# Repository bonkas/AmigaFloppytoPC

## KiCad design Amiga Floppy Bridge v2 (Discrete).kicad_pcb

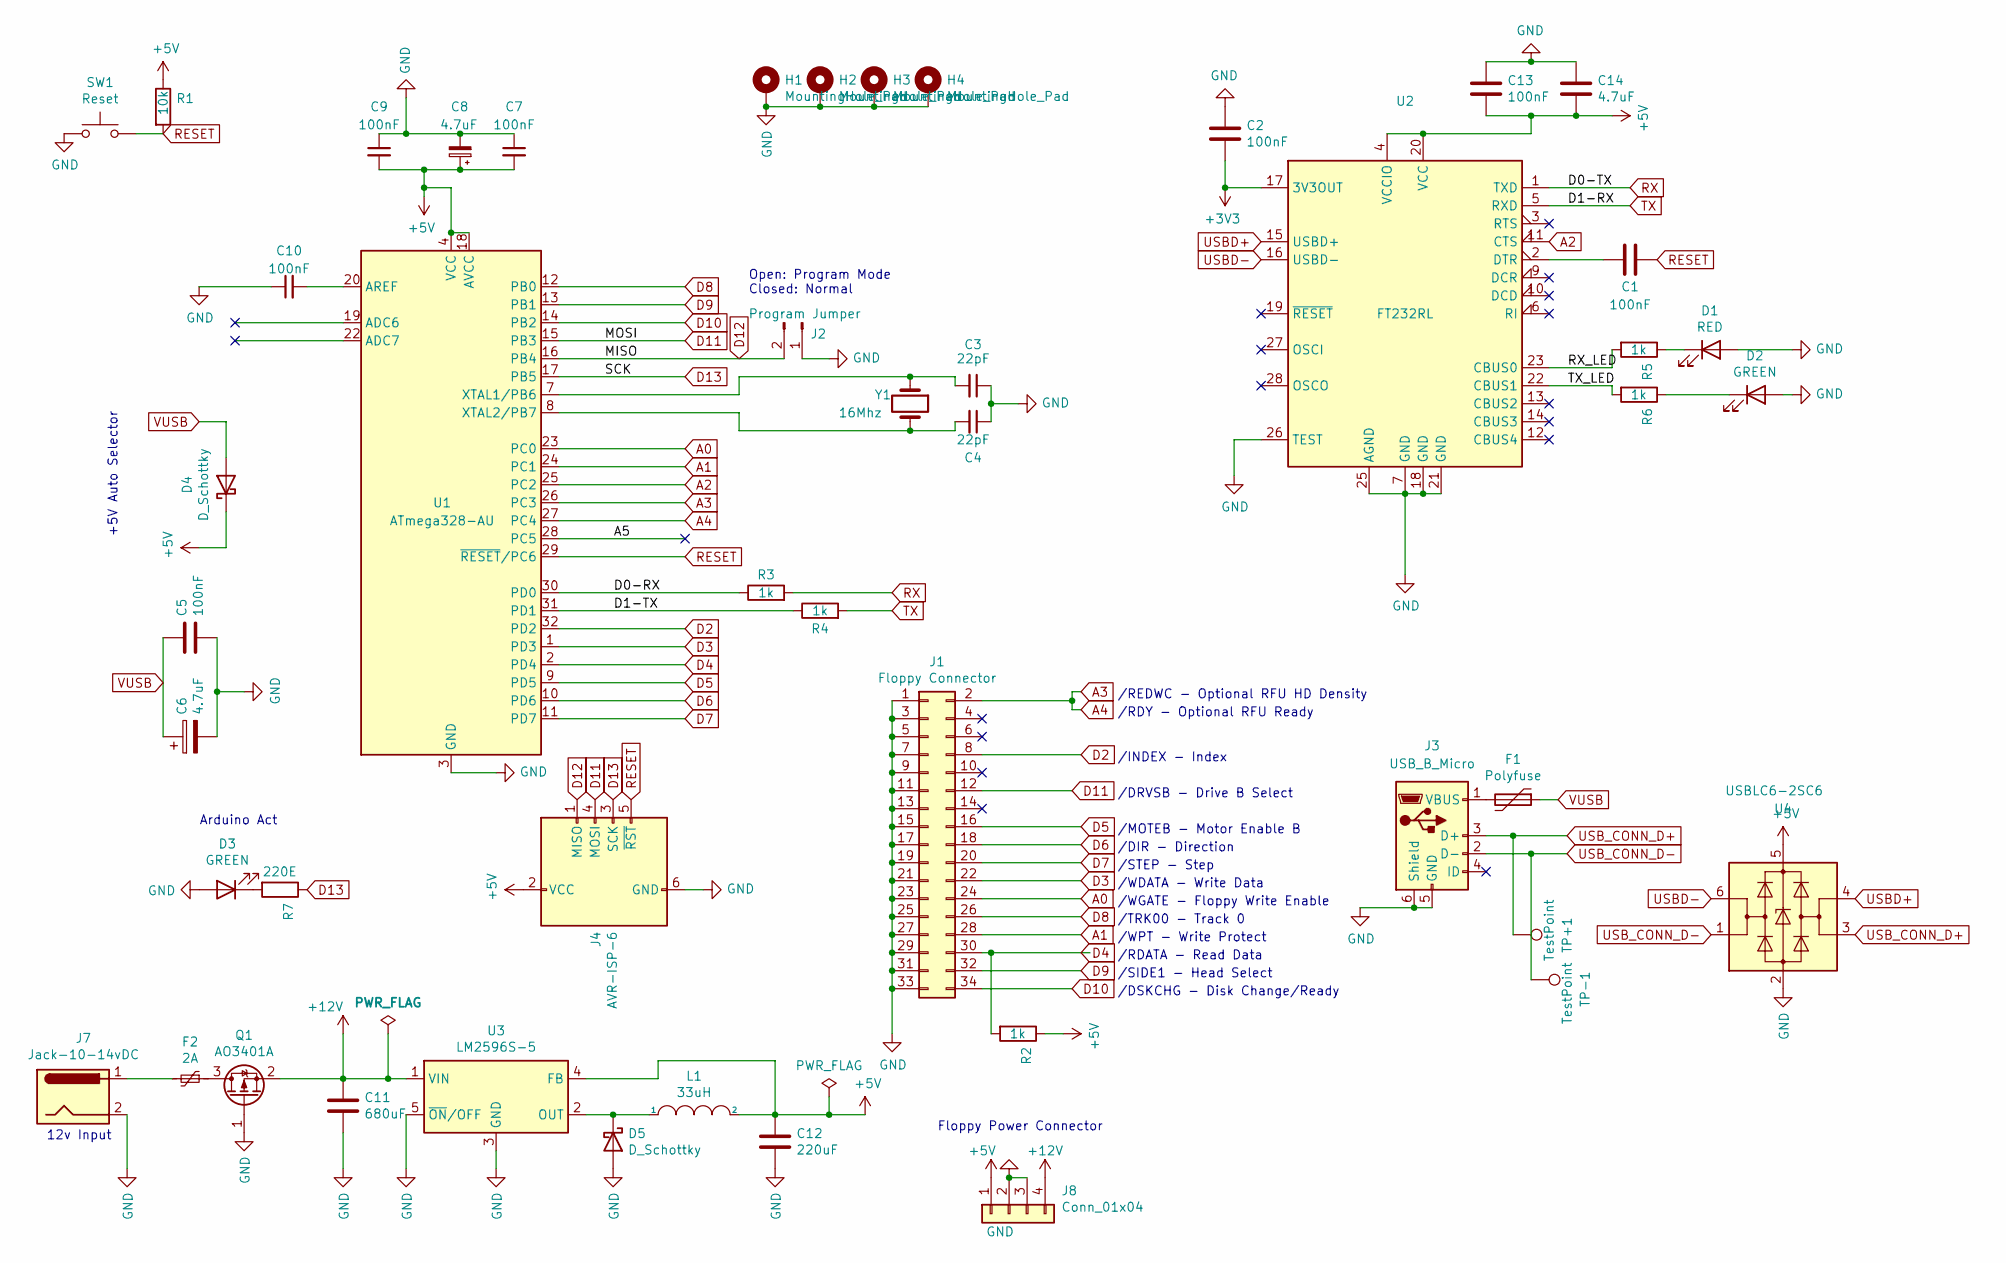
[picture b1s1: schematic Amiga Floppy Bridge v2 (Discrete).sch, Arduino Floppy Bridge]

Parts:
C1, C2, C5, C7, C9, C10, C13: 100nF; C_0805_2012Metric_Pad1.18x1.45mm_HandSolder; LCSC Part C49678
C3, C4: 22pF; C_0805_2012Metric_Pad1.18x1.45mm_HandSolder; LCSC Part C1804
C6, C8, C14: 4.7uF; C_0805_2012Metric_Pad1.18x1.45mm_HandSolder; LCSC Part C1779
C11: 680uF; CP_Elec_10x10; LCSC Part C249562
C12: 220uF; CP_Elec_6.3x7.7; LCSC Part C127327
D1: RED; LED_0201_0603Metric_Pad0.64x0.40mm_HandSolder; LCSC Part C2286
D2, D3: GREEN; LED_0201_0603Metric_Pad0.64x0.40mm_HandSolder; LCSC Part C72043
D4: D_Schottky; D_SMA-SMB_Universal_Handsoldering; LCSC Part C64989
D5: D_Schottky; D_SMA-SMB_Universal_Handsoldering; LCSC Part C22452
F1: Polyfuse; Fuse_0805_2012Metric_Pad1.15x1.40mm_HandSolder; LCSC Part C70061
F2: 2A; Fuse_1812_4532Metric; LCSC Part C69691
H1, H2, H3, H4: MountingHole_Pad; MountingHole_3.2mm_M3_Pad_Via
J1: Floppy Connector; PinHeader_2x17_P2.54mm_Vertical
J2: Program Jumper; PinHeader_1x02_P2.54mm_Vertical
J3: USB_B_Micro; USB_Micro-B_Molex_47346-0001; LCSC Part C132560
J4: AVR-ISP-6; PinHeader_2x03_P2.54mm_Vertical
J7: Jack-10-14vDC; BarrelJack_Wuerth_6941xx301002
J8: Conn_01x04; PinHeader_1x04_P2.54mm_Vertical
L1: 33uH; YSPI1365-470M; LCSC Part C329385
Q1: AO3401A; SOT-23
R1: 10k; R_0805_2012Metric_Pad1.20x1.40mm_HandSolder; LCSC Part C17414
R2, R3, R4, R5, R6: 1k; R_0805_2012Metric_Pad1.20x1.40mm_HandSolder; LCSC Part C17513
R7: 220E; R_0805_2012Metric_Pad1.20x1.40mm_HandSolder; LCSC Part C17557
SW1: Reset; SW_PUSH_6mm
TP+1: TestPoint
TP-1: TestPoint
U1: ATmega328-AU; TQFP-32_7x7mm_P0.8mm
U2: FT232RL; SSOP-28_5.3x10.2mm_P0.65mm
U3: LM2596S-5; TO-263-5_TabPin3; LCSC Part C347421
U4: USBLC6-2SC6; SOT-23-6; LCSC Part C7519
Y1: 16Mhz; Crystal_SMD_2520-4Pin_2.5x2.0mm

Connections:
+3V3: C2.1, U2.17 (3V3OUT)
+5V: C7.2, C8.1, C9.2, C12.1, C13.1, C14.1, D4.1 (K), J4.2 (VCC), J8.1, L1.2, R1.1, R2.1, U1.4 (VCC), U1.6 (VCC), U1.18 (AVCC), U2.4 (VCCIO), U2.20 (VCC), U3.4 (FB), U4.5 (VBUS)
+12V: C11.1, J8.4, Q1.2 (S), U3.1 (VIN)
/A5: U1.28 (PC5)
/D0-RX: R3.1, U1.30 (PD0)
/D1-TX: R4.1, U1.31 (PD1)
/RX_LED: R5.2, U2.23 (CBUS0)
/TX_LED: R6.2, U2.22 (CBUS1)
A0: J1.24, U1.23 (PC0)
A1: J1.28, U1.24 (PC1)
A2: U1.25 (PC2), U2.11 (CTS)
A3: J1.2, U1.26 (PC3), U1.27 (PC4)
D2: J1.8, U1.32 (PD2)
D3: J1.22, U1.1 (PD3)
D4: J1.30, R2.2, U1.2 (PD4)
D5: J1.16, U1.9 (PD5)
D6: J1.18, U1.10 (PD6)
D7: J1.20, U1.11 (PD7)
D8: J1.26, U1.12 (PB0)
D9: J1.32, U1.13 (PB1)
D10: J1.34, U1.14 (PB2)
D11: J1.12, J4.4 (MOSI), U1.15 (PB3)
D12: J2.2, J4.1 (MISO), U1.16 (PB4)
D13: J4.3 (SCK), R7.1, U1.17 (PB5)
GND: C2.2, C3.1, C4.1, C5.2, C6.2, C7.1, C8.2, C9.1, C10.1, C11.2, C12.2, C13.2, C14.2, D1.2 (A), D2.2 (A), D3.2 (A), D5.2 (A), H1.1, H2.1, H3.1, H4.1, J1.1, J1.3, J1.5, J1.7, J1.9, J1.11, J1.13, J1.15, J1.17, J1.19, J1.21, J1.23, J1.25, J1.27, J1.29, J1.31, J1.33, J2.1, J3.5 (GND), J3.6 (Shield), J4.6 (GND), J7.2, J8.2, J8.3, Q1.1 (G), SW1.1, U1.3 (GND), U1.5 (GND), U1.21 (GND), U2.7 (GND), U2.18 (GND), U2.21 (GND), U2.25 (AGND), U2.26 (TEST), U3.3 (GND), U3.5 (~ON~/OFF), U4.2 (GND)
unnamed: C1.2, U2.2 (DTR)
unnamed: C3.2, U1.7 (XTAL1/PB6), Y1.1
unnamed: C4.2, U1.8 (XTAL2/PB7), Y1.2
unnamed: C10.2, U1.20 (AREF)
unnamed: D1.1 (K), R5.1
unnamed: D2.1 (K), R6.1
unnamed: D3.1 (K), R7.2
unnamed: D5.1 (K), L1.1, U3.2 (OUT)
unnamed: F1.2, J3.1 (VBUS)
unnamed: F2.1, Q1.3 (D)
unnamed: F2.2, J7.1
RESET: C1.1, J4.5 (~RST), R1.2, SW1.2, U1.29 (~RESET~/PC6)
RX: R3.2, U2.1 (TXD)
TX: R4.2, U2.5 (RXD)
USBD+: U2.15 (USBD+), U4.4 (I/O2)
USBD-: U2.16 (USBD-), U4.6 (I/O1)
USB_CONN_D+: J3.3 (D+), TP+1.1, U4.3 (I/O2)
USB_CONN_D-: J3.2 (D-), TP-1.1, U4.1 (I/O1)
VUSB: C5.1, C6.1, D4.2 (A), F1.1

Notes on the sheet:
Open: Program Mode Closed: Normal
+5V Auto Selector
/INDEX - Index
/DRVSB - Drive B Select
/MOTEB - Motor Enable B
/DIR - Direction
/STEP - Step
/WDATA - Write Data
/WGATE - Floppy Write Enable
/TRK00 - Track 0
/WPT - Write Protect
/RDATA - Read Data
/SIDE1 - Head Select
/DSKCHG - Disk Change/Ready
/REDWC - Optional RFU HD Density
/RDY - Optional RFU Ready
12v Input
Floppy Power Connector
Arduino Act

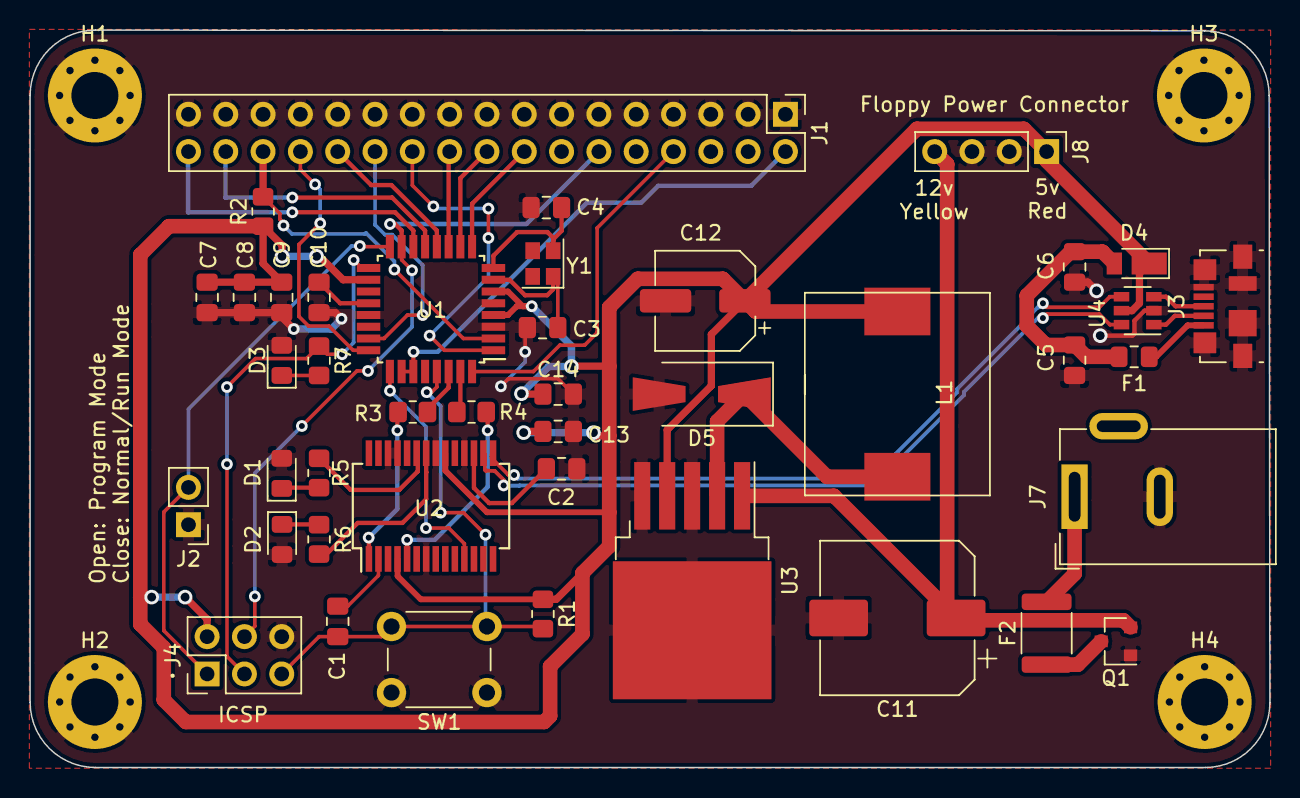
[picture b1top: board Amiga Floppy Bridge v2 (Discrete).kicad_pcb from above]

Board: 2 copper layers, 84.4 x 50.2 mm, 46 parts (0 on the bottom side), 43 nets.
